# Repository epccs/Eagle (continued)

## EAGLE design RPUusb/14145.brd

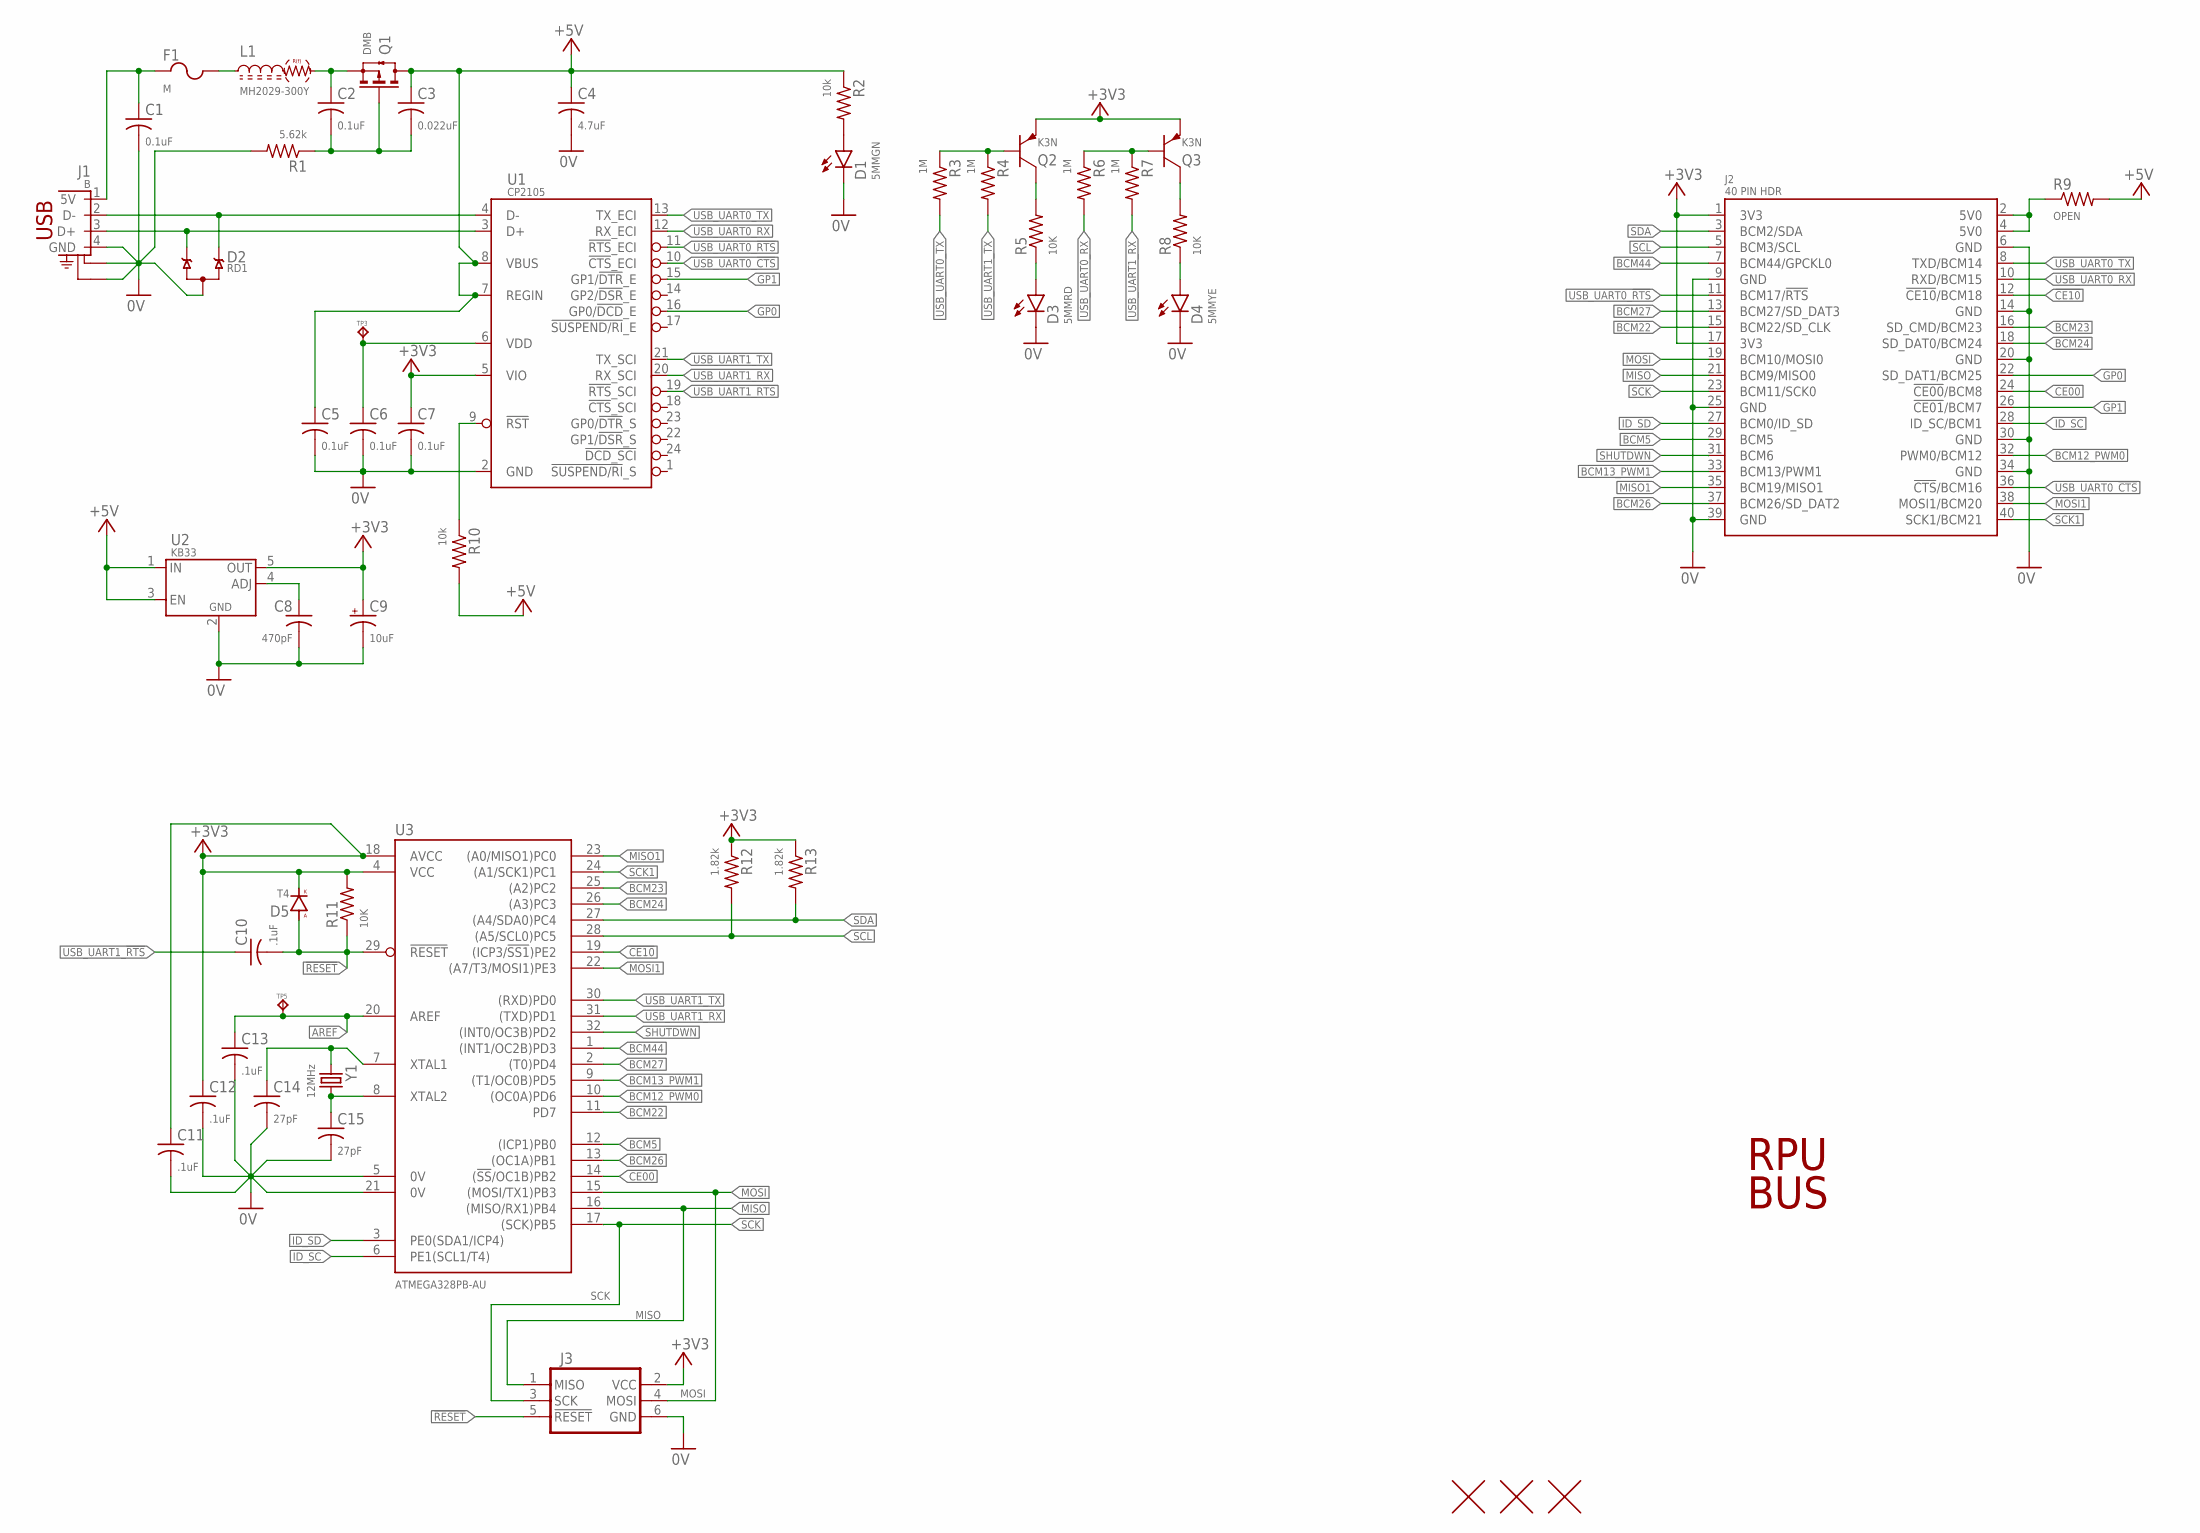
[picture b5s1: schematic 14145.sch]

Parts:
C1, C2, C5, C6, C7: 0.1uF; C0603(1608)
C3: 0.022uF; C0603(1608)
C4: 4.7uF; C1206(3216)
C8: 470pF; C0603(1608)
C9: 10uF; 3216
C10, C11, C12, C13: .1uF; C0603(1608)
C14, C15: 27pF; C0603(1608)
D1: 5MMGN; LED5MM
D2: RD1; SOT23
D3: 5MMRD; LED5MM
D4: 5MMYE; LED5MM
D5: T4; SOD123
F1: M; C1210(3225)
J1: B; USB-B-PTH
J2: 40 PIN HDR; RASPI_ZERO_H40PIN
J3: ISP-SPIPTH; ISP
L1: MH2029-300Y; C0805(2012)
Q1: DMB; SOT23
Q2, Q3: K3N; SOT23
R1: 5.62k; C0805(2012)
R2, R10: 10k; C0805(2012)
R3, R4, R6, R7: 1M; C0805(2012)
R5, R8, R11: 10K; C0805(2012)
R9: OPEN; C0805(2012)
R12, R13: 1.82k; C0805(2012)
TP3, TP5: TPPAD1-08; P1-08
U1: CP2105; QFN24
U2: KB33; SOT23-5,SOT25
U3: ATMEGA328PB-AU; TQFP32-08
U$2, U$3, U$4: FIDUCIAL1.27; FIDUCIAL-1.27
Y1: 12MHz; CSM-3X

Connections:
0V: C1.2, C4.2, C5.2, C6.2, C7.2, C8.2, C9.-, C11.2, C12.2, C13.2, C14.2, C15.2, D1.K, D2.3 (A), D3.K, D4.K, J1.4 (GND), J1.S1 (CHASSIS1), J1.S2 (CHASSIS2), J2.6 (GND), J2.9 (GND), J2.14 (GND), J2.20 (GND), J2.25 (GND), J2.30 (GND), J2.34 (GND), J2.39 (GND), J3.6 (GND), R1.2, U1.2 (GND), U2.2 (GND), U3.5 (0V), U3.21 (0V)
5V0@2: J2.2 (5V0), J2.4 (5V0), R9.1
!CE00!: J2.24 (!CE00!/BCM8), U3.14 ((!SS!/OC1B)PB2)
!CE10!: J2.12 (!CE10!/BCM18), U3.19 ((ICP3/!SS1!)PE2)
!RESET: C10.2, D5.A, J3.5 (!RESET), R11.1, U3.29 (!RESET)
+3V3: C7.1, C9.+, C11.1, C12.1, D5.C (K), J2.1 (3V3), J2.17 (3V3), J3.2 (VCC), Q2.E, Q3.E, R11.2, R12.1, R13.1, U1.5 (VIO), U2.5 (OUT), U3.4 (VCC), U3.18 (AVCC)
+5V: C3.1, C4.1, C5.1, Q1.3(D) (D), R2.1, R9.2, R10.2, U1.7 (REGIN), U1.8 (VBUS), U2.1 (IN), U2.3 (EN)
AREF: C13.1, TP5.TP, U3.20 (AREF)
BCM5: J2.29 (BCM5), U3.12 ((ICP1)PB0)
BCM12_PWM0: J2.32 (PWM0/BCM12), U3.10 ((OC0A)PD6)
BCM13_PWM1: J2.33 (BCM13/PWM1), U3.9 ((T1/OC0B)PD5)
BCM22: J2.15 (BCM22/SD_CLK), U3.11 (PD7)
BCM23: J2.16 (SD_CMD/BCM23), U3.25 ((A2)PC2)
BCM24: J2.18 (SD_DAT0/BCM24), U3.26 ((A3)PC3)
BCM26: J2.37 (BCM26/SD_DAT2), U3.13 ((OC1A)PB1)
BCM27: J2.13 (BCM27/SD_DAT3), U3.2 ((T0)PD4)
BCM44: J2.7 (BCM44/GPCKL0), U3.1 ((INT1/OC2B)PD3)
D+: D2.1 (C1), J1.3 (D+), U1.3 (D+)
D-: D2.2 (C2), J1.2 (D-), U1.4 (D-)
FTDI3V3: C6.1, TP3.TP, U1.6 (VDD)
GP0: J2.22 (SD_DAT1/BCM25), U1.16 (GP0/!DCD!_E)
GP1: J2.26 (!CE01!/BCM7), U1.15 (GP1/!DTR!_E)
ID_SC: J2.28 (ID_SC/BCM1), U3.6 (PE1(SCL1/T4))
ID_SD: J2.27 (BCM0/ID_SD), U3.3 (PE0(SDA1/ICP4))
MISO: J2.21 (BCM9/MISO0), J3.1 (MISO), U3.16 ((MISO/RX1)PB4)
MISO1: J2.35 (BCM19/MISO1), U3.23 ((A0/MISO1)PC0)
MOSI: J2.19 (BCM10/MOSI0), J3.4 (MOSI), U3.15 ((MOSI/TX1)PB3)
MOSI1: J2.38 (MOSI1/BCM20), U3.22 ((A7/T3/MOSI1)PE3)
unnamed: D1.A, R2.2
unnamed: D4.A, R8.1
unnamed: Q3.C, R8.2
unnamed: C1.1, F1.1, J1.1 (5V)
unnamed: F1.2, L1.1
unnamed: D3.A, R5.1
unnamed: R10.1, U1.9 (!RST!)
unnamed: Q2.C, R5.2
unnamed: Q2.B, R3.1, R4.1
unnamed: Q3.B, R6.1, R7.1
unnamed: C8.1, U2.4 (ADJ)
unnamed: C2.1, L1.2, Q1.2(S) (S)
unnamed: C2.2, C3.2, Q1.1(G) (G), R1.1
SCK: J2.23 (BCM11/SCK0), J3.3 (SCK), U3.17 ((SCK)PB5)
SCK1: J2.40 (SCK1/BCM21), U3.24 ((A1/SCK1)PC1)
SCL: J2.5 (BCM3/SCL), R12.2, U3.28 ((A5/SCL0)PC5)
SDA: J2.3 (BCM2/SDA), R13.2, U3.27 ((A4/SDA0)PC4)
SHUTDWN: J2.31 (BCM6), U3.32 ((INT0/OC3B)PD2)
USB_UART0_!CTS: J2.36 (!CTS!/BCM16), U1.10 (!CTS!_ECI)
USB_UART0_!RTS: J2.11 (BCM17/!RTS!), U1.11 (!RTS!_ECI)
USB_UART0_RX: J2.10 (RXD/BCM15), R6.2, U1.12 (RX_ECI)
USB_UART0_TX: J2.8 (TXD/BCM14), R3.2, U1.13 (TX_ECI)
USB_UART1_!RTS: C10.1, U1.19 (!RTS!_SCI)
USB_UART1_RX: R7.2, U1.20 (RX_SCI), U3.31 ((TXD)PD1)
USB_UART1_TX: R4.2, U1.21 (TX_SCI), U3.30 ((RXD)PD0)
XTAL1: C14.1, U3.7 (XTAL1), Y1.1
XTAL2: C15.1, U3.8 (XTAL2), Y1.2

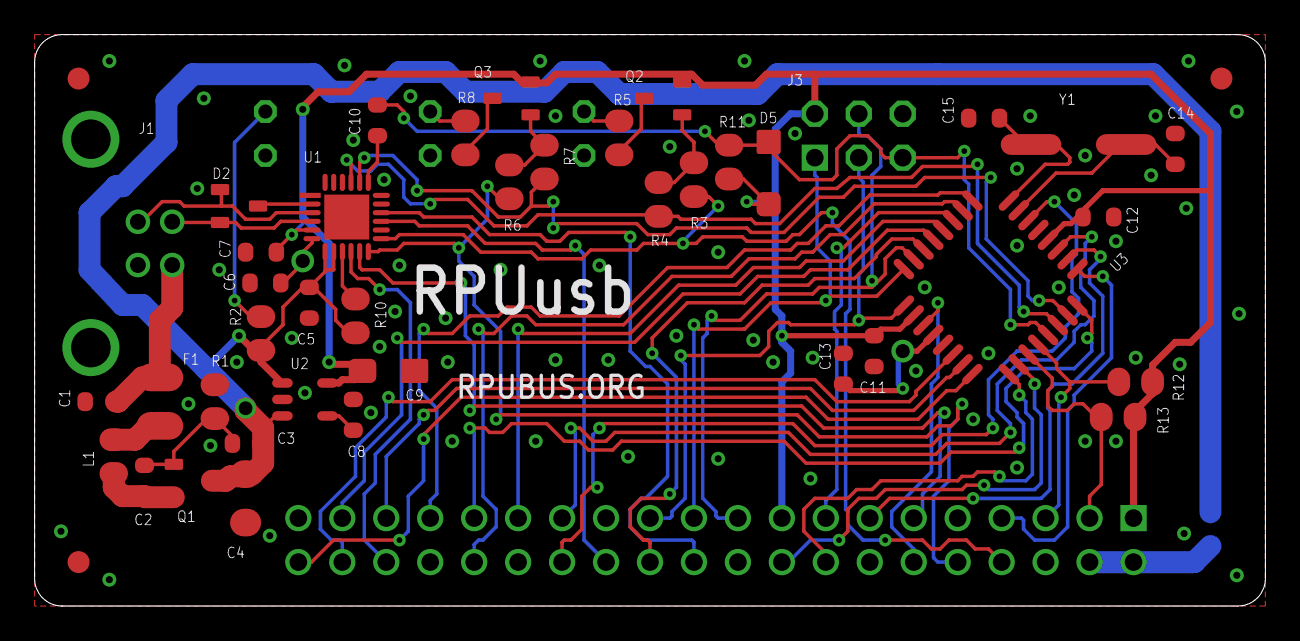
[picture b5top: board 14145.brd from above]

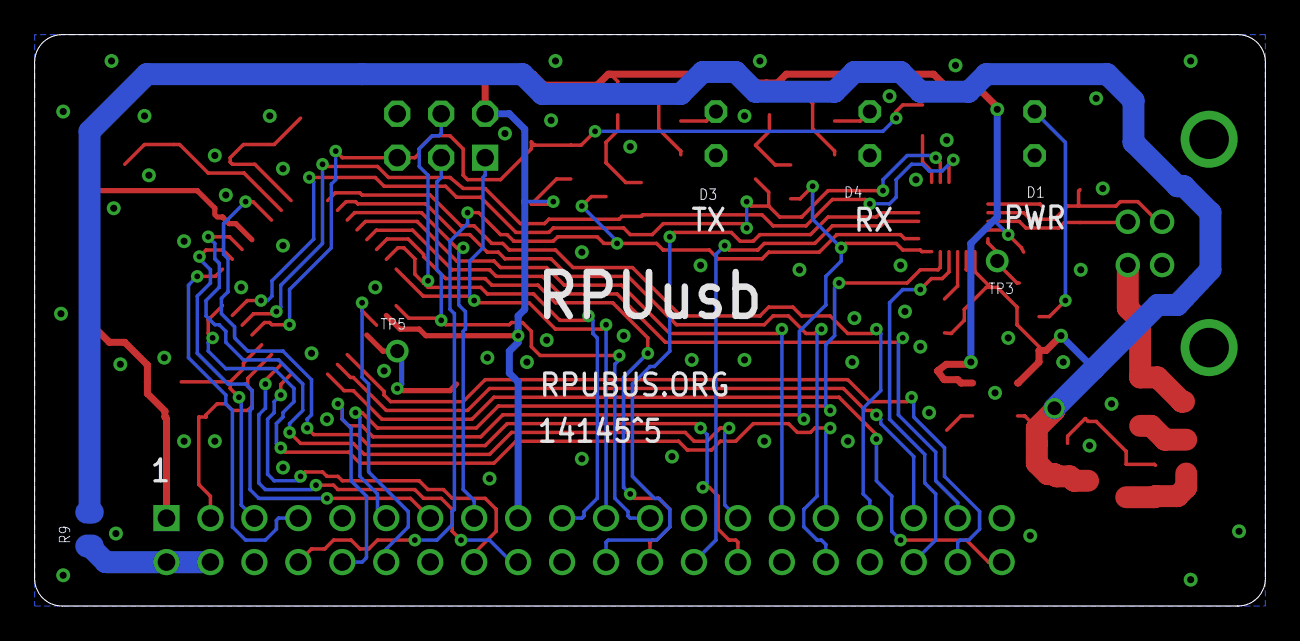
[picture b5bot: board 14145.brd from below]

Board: 2 copper layers, 71.1 x 33.0 mm, 50 parts (6 on the bottom side), 55 nets.

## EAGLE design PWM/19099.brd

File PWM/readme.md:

PWM

Sixteen 22mA current sources controled with PCA9685 over I2C

TBD https://oshpark.com/shared_projects/???

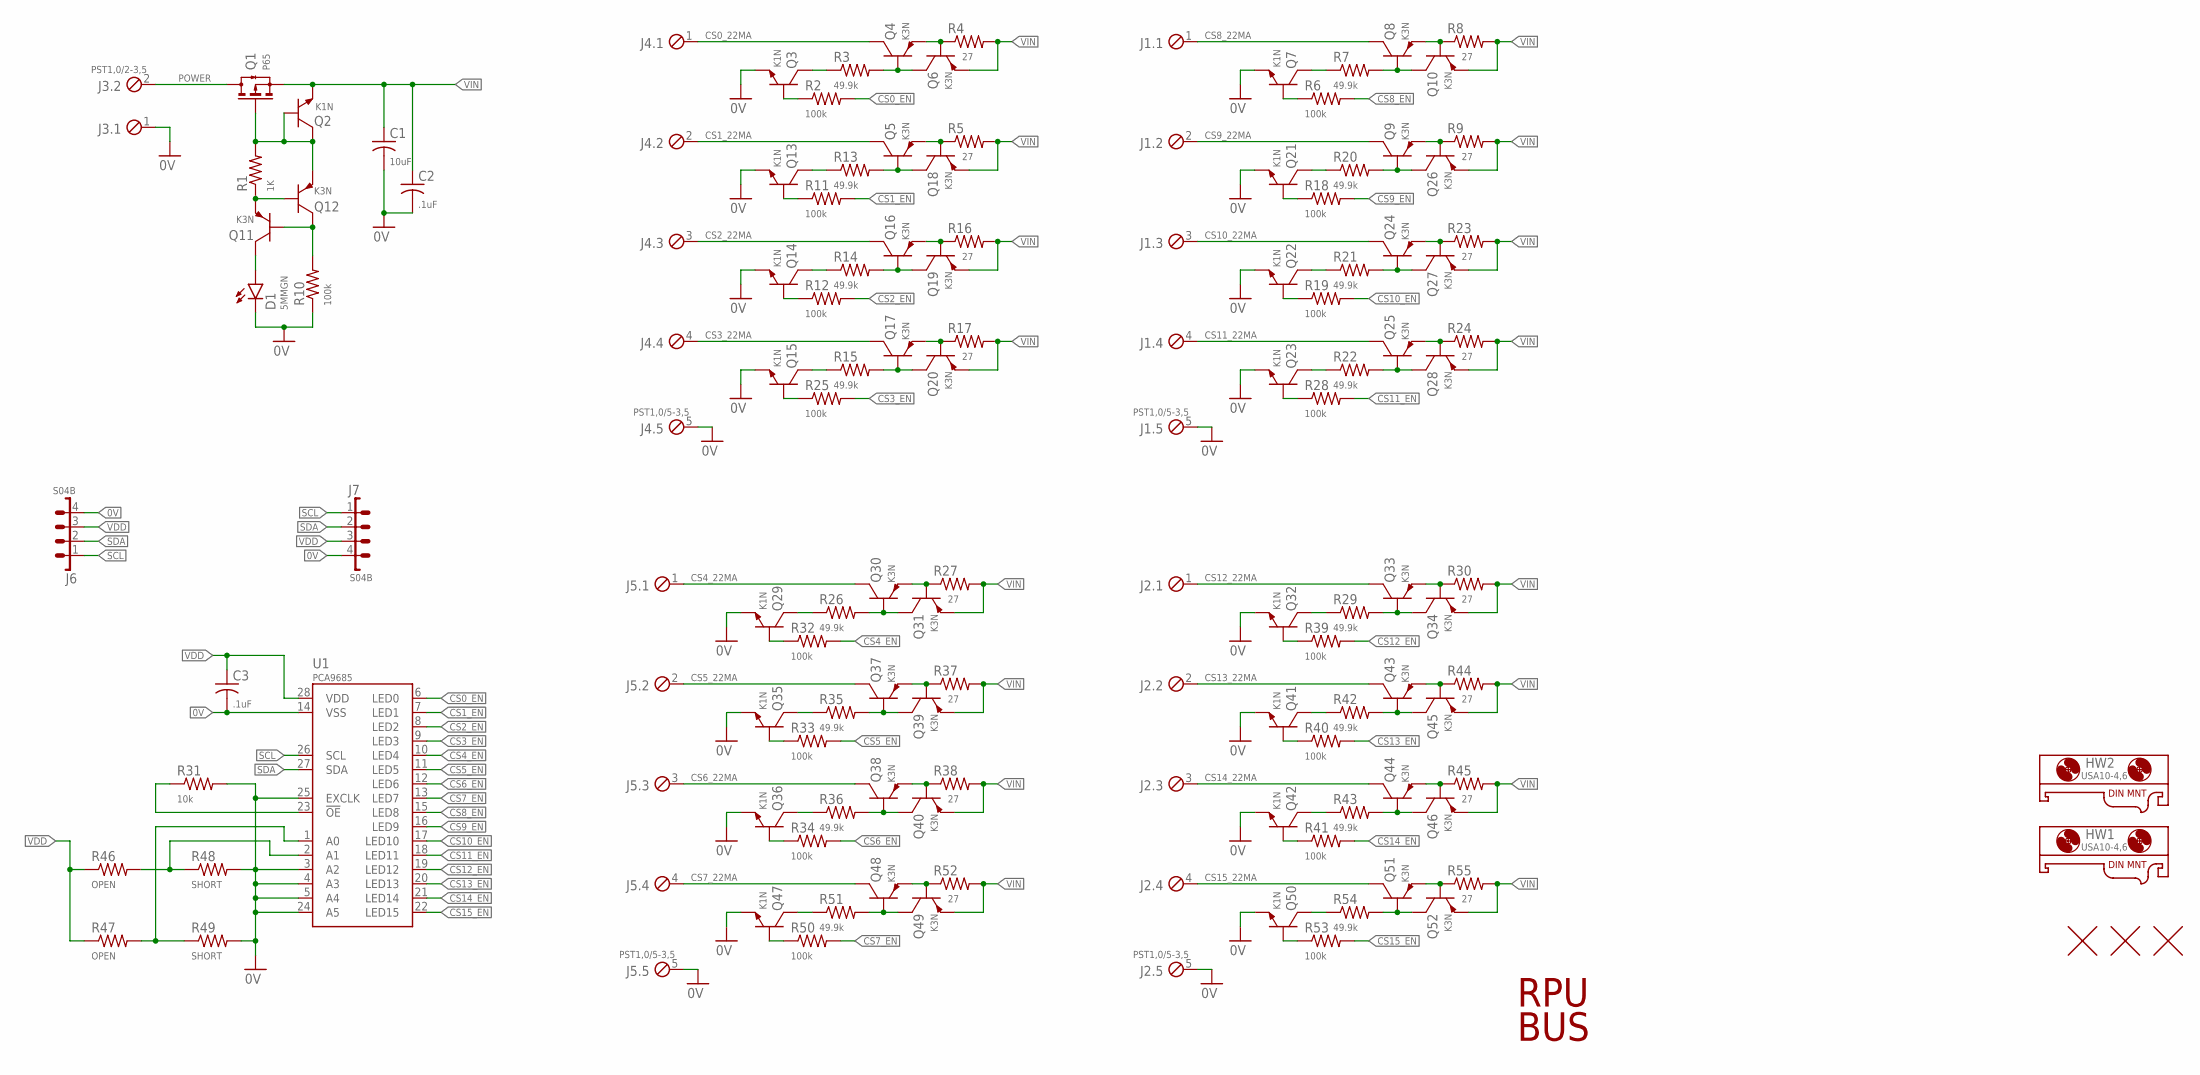
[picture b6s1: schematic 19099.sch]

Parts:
C1: 10uF; C1206(3216)
C2: .1uF; C0805(2012)
C3: .1uF; C0603(1608)
D1: 5MMGN; LED5MM
HW1, HW2: USA10-4,6; USA10
J1, J2, J4, J5: PST1,0/5-3,5; MCV5
J3: PST1,0/2-3,5; MCV2
J6, J7: S04B; B04B
Q1: P65; SOT23
Q2, Q3, Q7, Q13, Q14, Q15, Q21, Q22, Q23, Q29, Q32, Q35, Q36, Q41, Q42, Q47, Q50: K1N; SOT23
Q4, Q5, Q6, Q8, Q9, Q10, Q11, Q12, Q16, Q17, Q18, Q19, Q20, Q24, Q25, Q26, Q27, Q28, Q30, Q31, Q33, Q34, Q37, Q38, Q39, Q40, Q43, Q44, Q45, Q46, Q48, Q49, Q51, Q52: K3N; SOT23
R1: 1K; C0805(2012)
R2, R6, R10, R11, R12, R18, R19, R25, R28, R32, R33, R34, R39, R40, R41, R50, R53: 100k; C0805(2012)
R3, R7, R13, R14, R15, R20, R21, R22, R26, R29, R35, R36, R42, R43, R51, R54: 49.9k; C0805(2012)
R4, R5, R8, R9, R16, R17, R23, R24, R27, R30, R37, R38, R44, R45, R52, R55: 27; C0805(2012)
R31: 10k; C0805(2012)
R46, R47: OPEN; C0805(2012)
R48, R49: SHORT; C0805(2012)
U1: PCA9685; 28TSSOP
U$2, U$3, U$4: FIDUCIAL1.27; FIDUCIAL-1.27

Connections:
0V: C1.2, C2.2, C3.2, D1.K, J1.5, J2.5, J3.1, J4.5, J5.5, J6.4, J7.4, Q3.E, Q7.E, Q13.E, Q14.E, Q15.E, Q21.E, Q22.E, Q23.E, Q29.E, Q32.E, Q35.E, Q36.E, Q41.E, Q42.E, Q47.E, Q50.E, R10.1, R31.2, R48.2, R49.2, U1.3 (A2), U1.4 (A3), U1.5 (A4), U1.14 (VSS), U1.24 (A5), U1.25 (EXCLK)
A0: R47.2, R49.1, U1.1 (A0)
A1: R46.2, R48.1, U1.2 (A1)
CS0_22MA: J4.1, Q4.C
CS0_EN: R2.2, U1.6 (LED0)
CS1_22MA: J4.2, Q5.C
CS1_EN: R11.2, U1.7 (LED1)
CS2_22MA: J4.3, Q16.C
CS2_EN: R12.2, U1.8 (LED2)
CS3_22MA: J4.4, Q17.C
CS3_EN: R25.2, U1.9 (LED3)
CS4_22MA: J5.1, Q30.C
CS4_EN: R32.2, U1.10 (LED4)
CS5_22MA: J5.2, Q37.C
CS5_EN: R33.2, U1.11 (LED5)
CS6_22MA: J5.3, Q38.C
CS6_EN: R34.2, U1.12 (LED6)
CS7_22MA: J5.4, Q48.C
CS7_EN: R50.2, U1.13 (LED7)
CS8_22MA: J1.1, Q8.C
CS8_EN: R6.2, U1.15 (LED8)
CS9_22MA: J1.2, Q9.C
CS9_EN: R18.2, U1.16 (LED9)
CS10_22MA: J1.3, Q24.C
CS10_EN: R19.2, U1.17 (LED10)
CS11_22MA: J1.4, Q25.C
CS11_EN: R28.2, U1.18 (LED11)
CS12_22MA: J2.1, Q33.C
CS12_EN: R39.2, U1.19 (LED12)
CS13_22MA: J2.2, Q43.C
CS13_EN: R40.2, U1.20 (LED13)
CS14_22MA: J2.3, Q44.C
CS14_EN: R41.2, U1.21 (LED14)
CS15_22MA: J2.4, Q51.C
CS15_EN: R53.2, U1.22 (LED15)
unnamed: Q4.E, Q6.B, R4.1
unnamed: Q3.B, R2.1
unnamed: Q5.E, Q18.B, R5.1
unnamed: Q5.B, Q18.C, R13.2
unnamed: Q11.B, Q12.C, R10.2
unnamed: Q1.1(G) (G), Q2.B, Q2.C, Q12.E, R1.2
unnamed: D1.A, Q11.C
unnamed: Q13.C, R13.1
unnamed: Q4.B, Q6.C, R3.2
unnamed: Q11.E, Q12.B, R1.1
unnamed: Q13.B, R11.1
unnamed: Q16.E, Q19.B, R16.1
unnamed: Q16.B, Q19.C, R14.2
unnamed: Q14.C, R14.1
unnamed: Q14.B, R12.1
unnamed: Q17.E, Q20.B, R17.1
unnamed: Q17.B, Q20.C, R15.2
unnamed: Q15.C, R15.1
unnamed: Q15.B, R25.1
unnamed: R31.1, U1.23 (!OE)
unnamed: Q30.E, Q31.B, R27.1
unnamed: Q30.B, Q31.C, R26.2
unnamed: Q29.C, R26.1
unnamed: Q29.B, R32.1
unnamed: Q37.E, Q39.B, R37.1
unnamed: Q37.B, Q39.C, R35.2
unnamed: Q35.C, R35.1
unnamed: Q35.B, R33.1
unnamed: Q38.E, Q40.B, R38.1
unnamed: Q38.B, Q40.C, R36.2
unnamed: Q36.C, R36.1
unnamed: Q36.B, R34.1
unnamed: Q48.E, Q49.B, R52.1
unnamed: Q48.B, Q49.C, R51.2
unnamed: Q47.C, R51.1
unnamed: Q47.B, R50.1
unnamed: Q8.E, Q10.B, R8.1
unnamed: Q8.B, Q10.C, R7.2
unnamed: Q7.C, R7.1
unnamed: Q7.B, R6.1
unnamed: Q9.E, Q26.B, R9.1
unnamed: Q9.B, Q26.C, R20.2
unnamed: Q21.C, R20.1
unnamed: Q21.B, R18.1
unnamed: Q24.E, Q27.B, R23.1
unnamed: Q24.B, Q27.C, R21.2
unnamed: Q22.C, R21.1
unnamed: Q22.B, R19.1
unnamed: Q25.E, Q28.B, R24.1
unnamed: Q25.B, Q28.C, R22.2
unnamed: Q23.C, R22.1
unnamed: Q23.B, R28.1
unnamed: Q33.E, Q34.B, R30.1
unnamed: Q33.B, Q34.C, R29.2
unnamed: Q32.C, R29.1
unnamed: Q32.B, R39.1
unnamed: Q43.E, Q45.B, R44.1
unnamed: Q3.C, R3.1
unnamed: Q43.B, Q45.C, R42.2
unnamed: Q41.C, R42.1
unnamed: Q41.B, R40.1
unnamed: Q44.E, Q46.B, R45.1
unnamed: Q44.B, Q46.C, R43.2
unnamed: Q42.C, R43.1
unnamed: Q42.B, R41.1
unnamed: Q51.E, Q52.B, R55.1
unnamed: Q51.B, Q52.C, R54.2
unnamed: Q50.C, R54.1
unnamed: Q50.B, R53.1
POWER: J3.2, Q1.3(D) (D)
SCL: J6.1, J7.1, U1.26 (SCL)
SDA: J6.2, J7.2, U1.27 (SDA)
VDD: C3.1, J6.3, J7.3, R46.1, R47.1, U1.28 (VDD)
VIN: C1.1, C2.1, Q1.2(S) (S), Q2.E, Q6.E, Q10.E, Q18.E, Q19.E, Q20.E, Q26.E, Q27.E, Q28.E, Q31.E, Q34.E, Q39.E, Q40.E, Q45.E, Q46.E, Q49.E, Q52.E, R4.2, R5.2, R8.2, R9.2, R16.2, R17.2, R23.2, R24.2, R27.2, R30.2, R37.2, R38.2, R44.2, R45.2, R52.2, R55.2

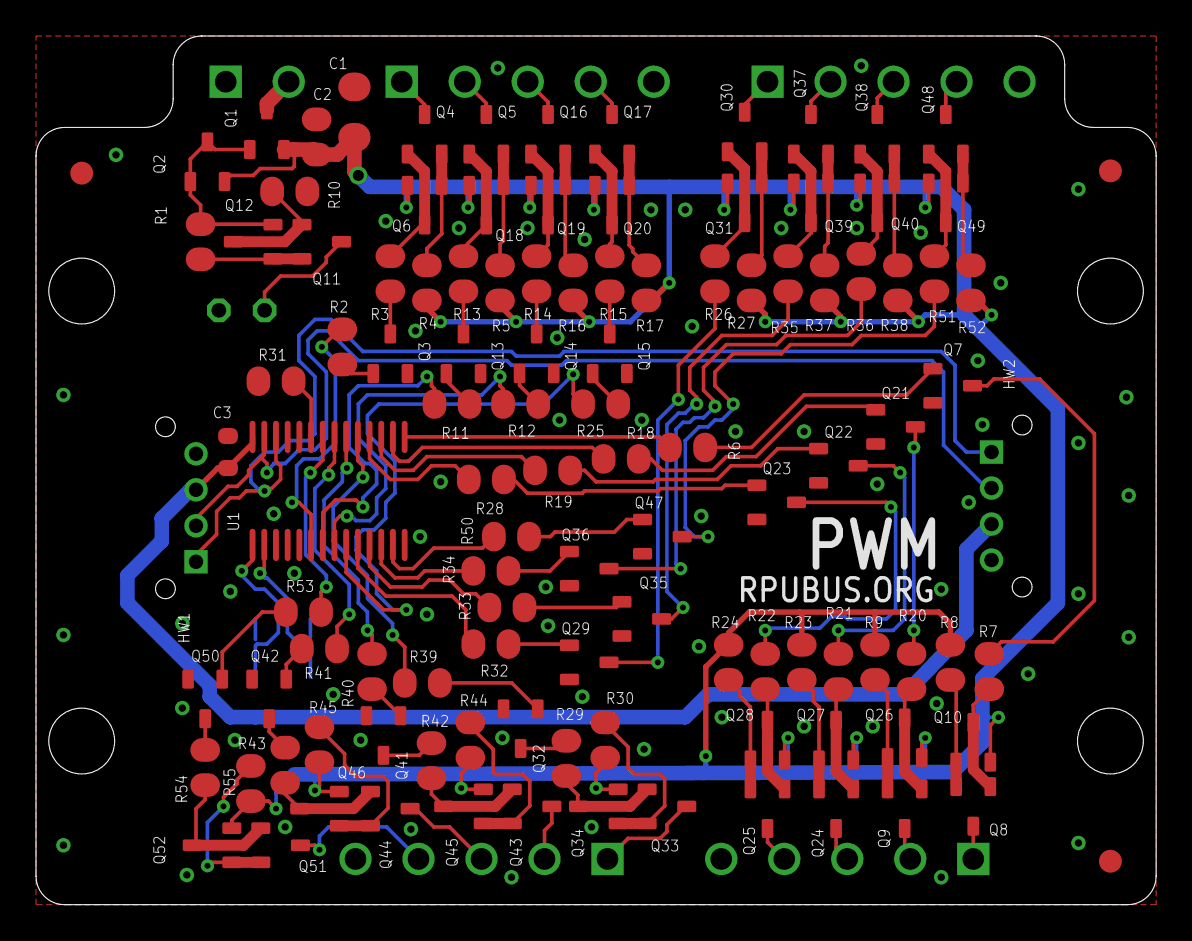
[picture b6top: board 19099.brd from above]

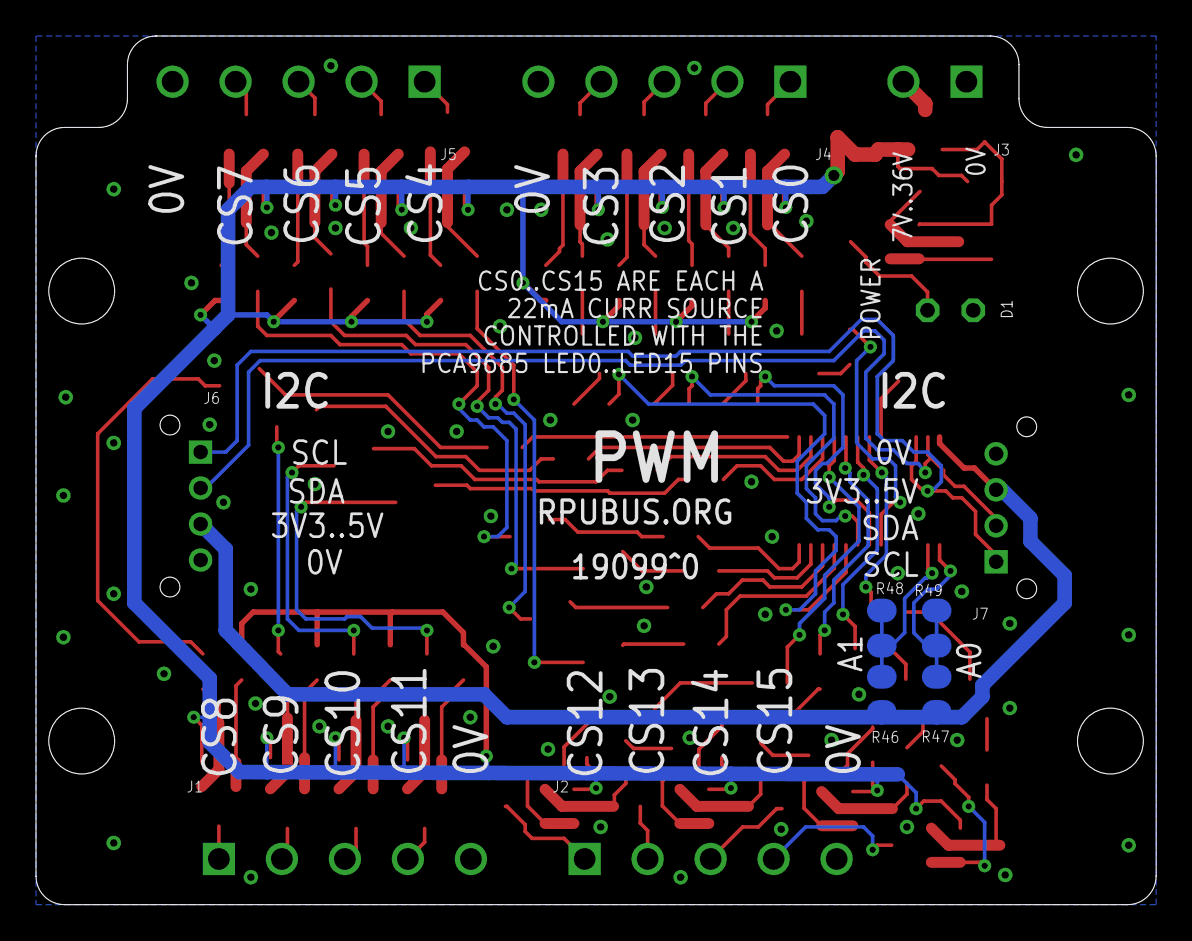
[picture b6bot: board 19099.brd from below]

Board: 2 copper layers, 62.2 x 48.3 mm, 124 parts (12 on the bottom side), 109 nets.

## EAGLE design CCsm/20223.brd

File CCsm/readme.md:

CCsm

Small constant current source for LED and other uses. Negative temperature coefficient (NTC) reduces current (thermal fold-back) with increasing temperature (about 0.2 %/K)

https://oshpark.com/shared_projects/9gUEmC1T

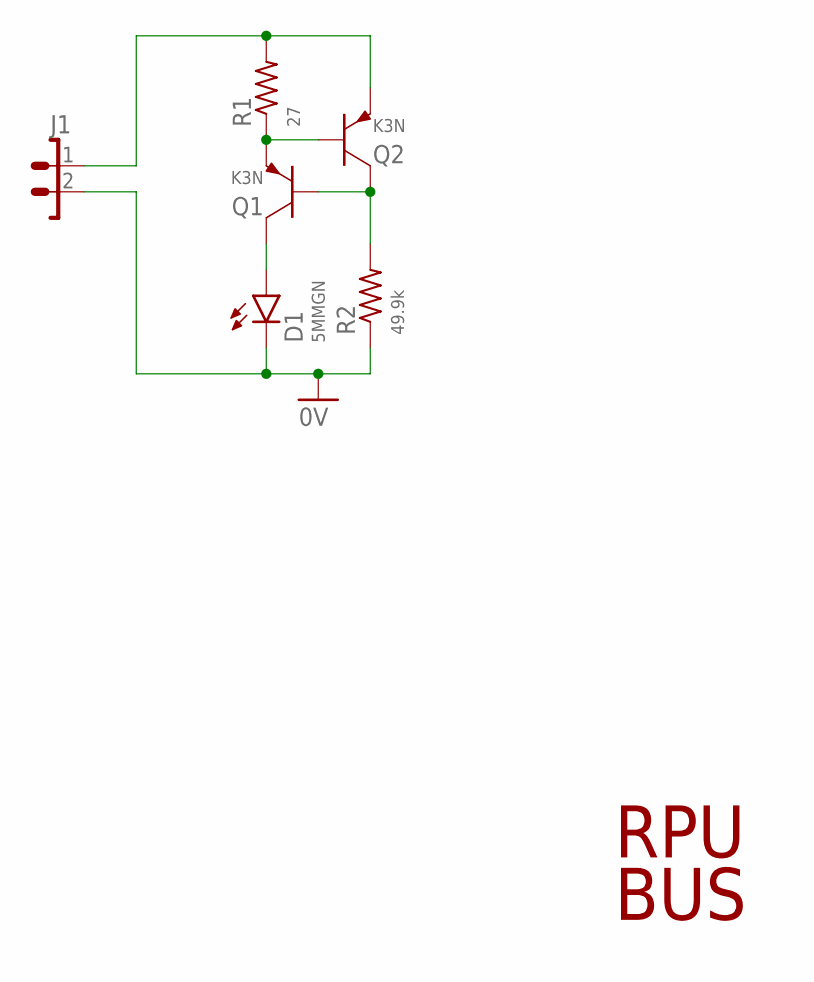
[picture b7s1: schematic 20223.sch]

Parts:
D1: 5MMGN; LED5MM
J1: 1X2
Q1, Q2: K3N; SOT23
R1: 27; C0805(2012)
R2: 49.9k; C0805(2012)

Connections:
0V: D1.K, J1.2, R2.1
unnamed: Q1.B, Q2.C, R2.2
unnamed: J1.1, Q2.E, R1.2
unnamed: D1.A, Q1.C
unnamed: Q1.E, Q2.B, R1.1

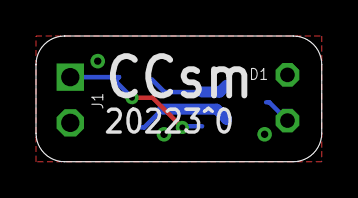
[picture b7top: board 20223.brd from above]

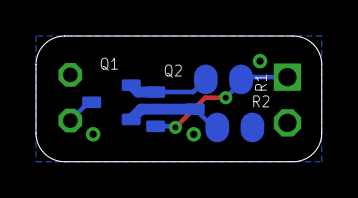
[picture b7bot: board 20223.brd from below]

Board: 2 copper layers, 15.9 x 7.0 mm, 6 parts (4 on the bottom side), 5 nets.

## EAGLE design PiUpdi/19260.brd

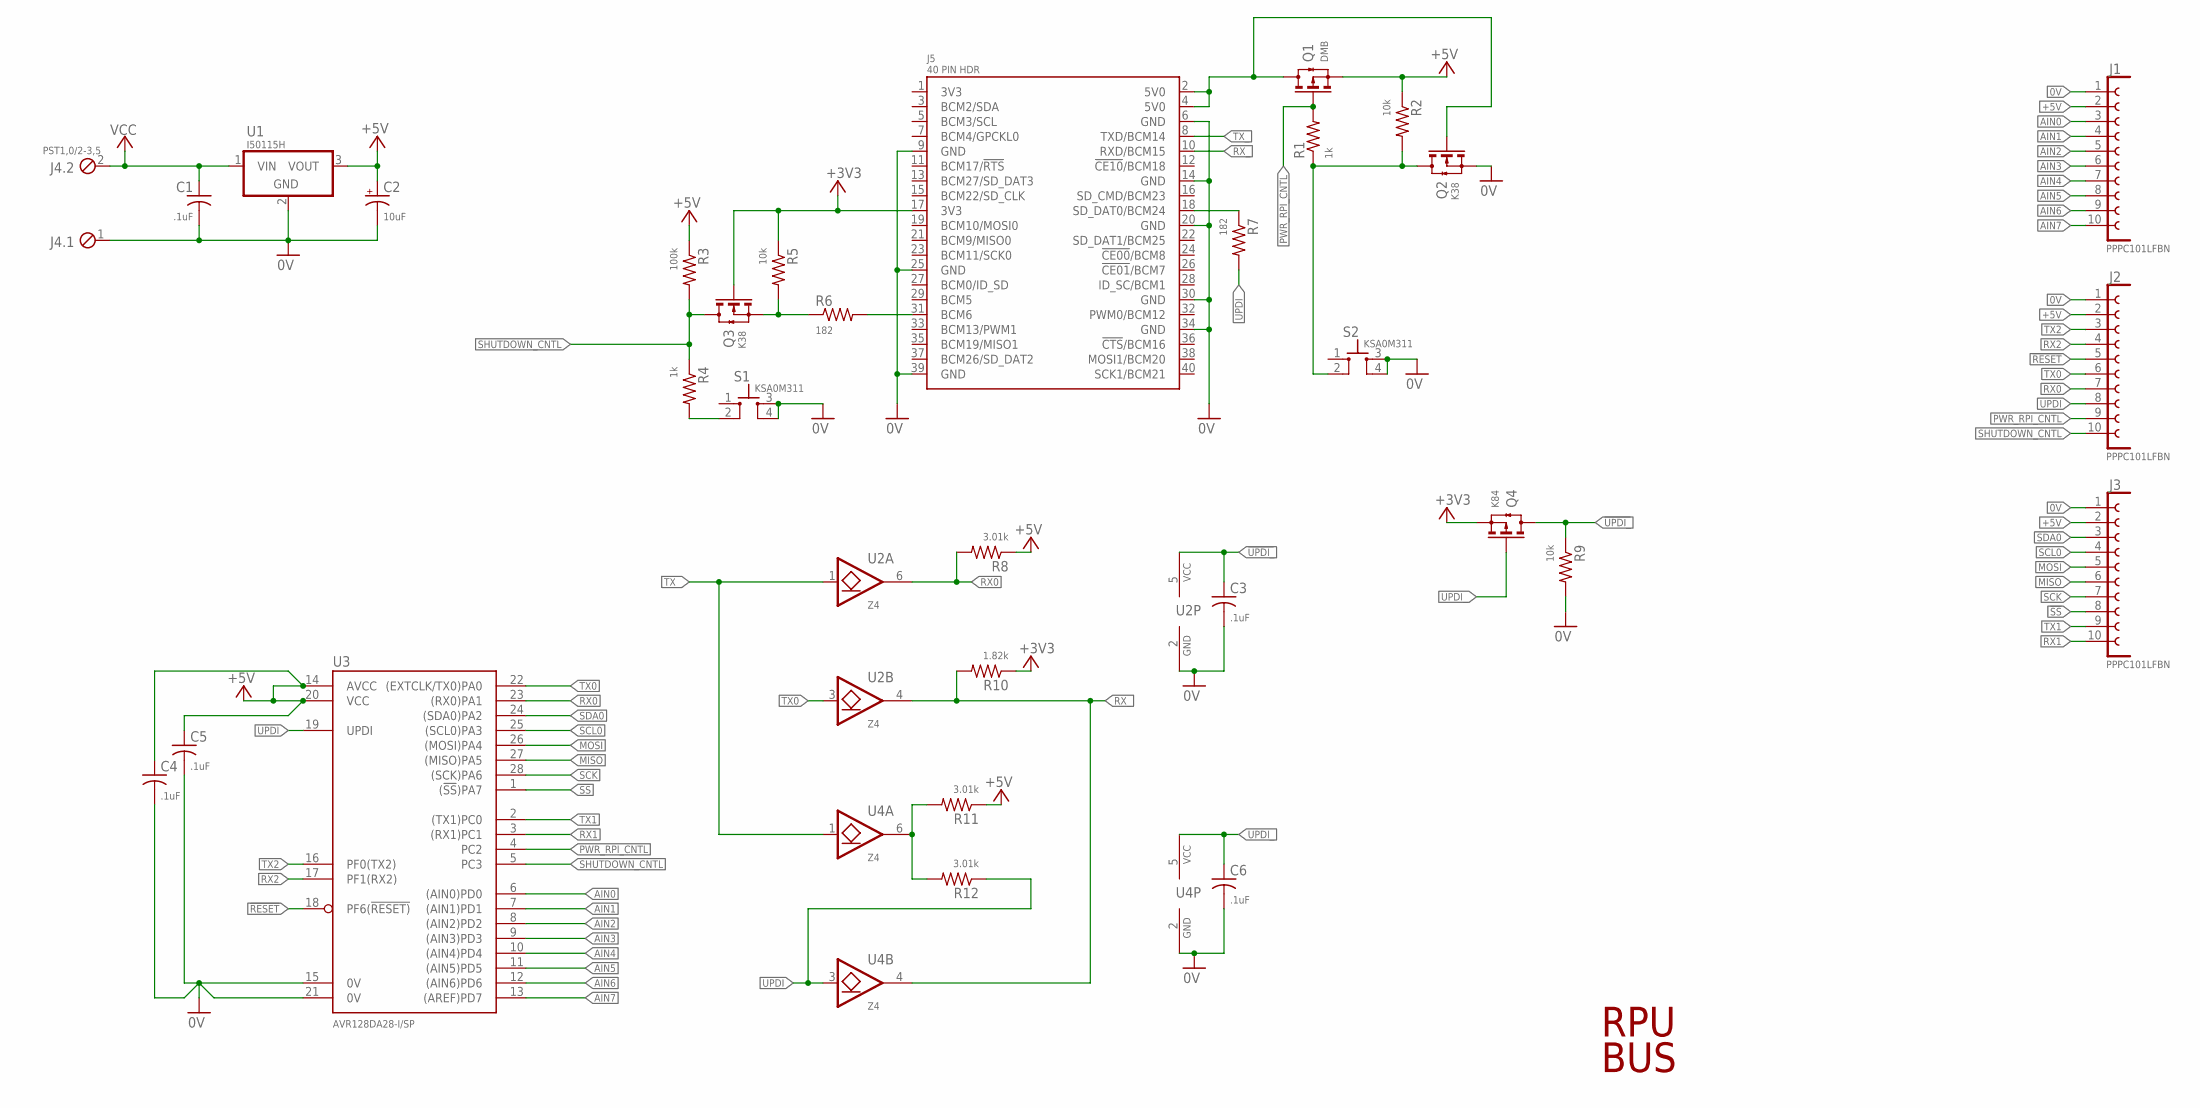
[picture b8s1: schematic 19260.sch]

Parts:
C1, C3, C4, C5, C6: .1uF; C0603(1608)
C2: 10uF; 3216
J1, J2, J3: PPPC101LFBN; F1X10
J4: PST1,0/2-3,5; MCV2
J5: 40 PIN HDR; RASPI_ZERO_H40PIN
Q1: DMB; SOT23
Q2, Q3: K38; SOT23
Q4: K84; SOT23
R1, R4: 1k; C0805(2012)
R2, R5, R9: 10k; C0805(2012)
R3: 100k; C0805(2012)
R6, R7: 182; C0805(2012)
R8, R11, R12: 3.01k; C0805(2012)
R10: 1.82k; C0805(2012)
S1, S2: KSA0M311; 0M311
U1: I50115H; OKI-78SR-H
U2, U4: Z4; SOT23-6,SOT26
U3: AVR128DA28-I/SP; DIL28-3

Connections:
0V: C1.2, C2.-, C3.2, C4.2, C5.2, C6.2, J1.1, J2.1, J3.1, J4.1, J5.6 (GND), J5.9 (GND), J5.14 (GND), J5.20 (GND), J5.25 (GND), J5.30 (GND), J5.34 (GND), J5.39 (GND), Q2.2(S) (S), R9.2, S1.3, S1.4, S2.3, S2.4, U1.2 (GND), U2.2 (GND), U3.15 (0V), U3.21 (0V), U4.2 (GND)
5V0@2: J5.2 (5V0), J5.4 (5V0), Q1.3(D) (D), Q2.1(G) (G)
!RESET: J2.5, U3.18 (PF6(!RESET))
!SS: J3.8, U3.1 ((!SS!)PA7)
!UPDI_: C3.1, Q4.3(D) (D), R9.1, U2.5 (VCC)
+3V3: J5.17 (3V3), Q3.1(G) (G), Q4.2(S) (S), R5.1, R10.1
+5V: C2.+, C4.1, C5.1, J1.2, J2.2, J3.2, Q1.2(S) (S), R2.1, R3.1, R8.1, R11.1, U1.3 (VOUT), U3.14 (AVCC), U3.20 (VCC)
AIN0: J1.3, U3.6 ((AIN0)PD0)
AIN1: J1.4, U3.7 ((AIN1)PD1)
AIN2: J1.5, U3.8 ((AIN2)PD2)
AIN3: J1.6, U3.9 ((AIN3)PD3)
AIN4: J1.7, U3.10 ((AIN4)PD4)
AIN5: J1.8, U3.11 ((AIN5)PD5)
AIN6: J1.9, U3.12 ((AIN6)PD6)
AIN7: J1.10, U3.13 ((AREF)PD7)
MISO: J3.6, U3.27 ((MISO)PA5)
MOSI: J3.5, U3.26 ((MOSI)PA4)
unnamed: R4.2, S1.2
unnamed: J5.18 (SD_DAT0/BCM24), R7.1
unnamed: J5.31 (BCM6), R6.2
unnamed: R11.2, R12.2, U4.6 (O)
unnamed: Q2.3(D) (D), R1.1, R2.2, S2.2
PWR_RPI_CNTL: J2.9, Q1.1(G) (G), R1.2, U3.4 (PC2)
RX0: J2.7, R8.2, U2.6 (O), U3.23 ((RX0)PA1)
RX1: J3.10, U3.3 ((RX1)PC1)
RX2: J2.4, U3.17 (PF1(RX2))
RX_: J5.10 (RXD/BCM15), R10.2, U2.4 (O), U4.4 (O)
SCK: J3.7, U3.28 ((SCK)PA6)
SCL0: J3.4, U3.25 ((SCL0)PA3)
SDA0: J3.3, U3.24 ((SDA0)PA2)
SHUTDOWN: Q3.2(S) (S), R5.2, R6.1
SHUTDOWN_CNTL: J2.10, Q3.3(D) (D), R3.2, R4.1, U3.5 (PC3)
TX0: J2.6, U2.3 (I), U3.22 ((EXTCLK/TX0)PA0)
TX1: J3.9, U3.2 ((TX1)PC0)
TX2: J2.3, U3.16 (PF0(TX2))
TX_: J5.8 (TXD/BCM14), U2.1 (I), U4.1 (I)
UPDI: J2.8, R12.1, U3.19 (UPDI), U4.3 (I)
UPDI_: C6.1, Q4.1(G) (G), R7.2, U4.5 (VCC)
VCC: C1.1, J4.2, U1.1 (VIN)

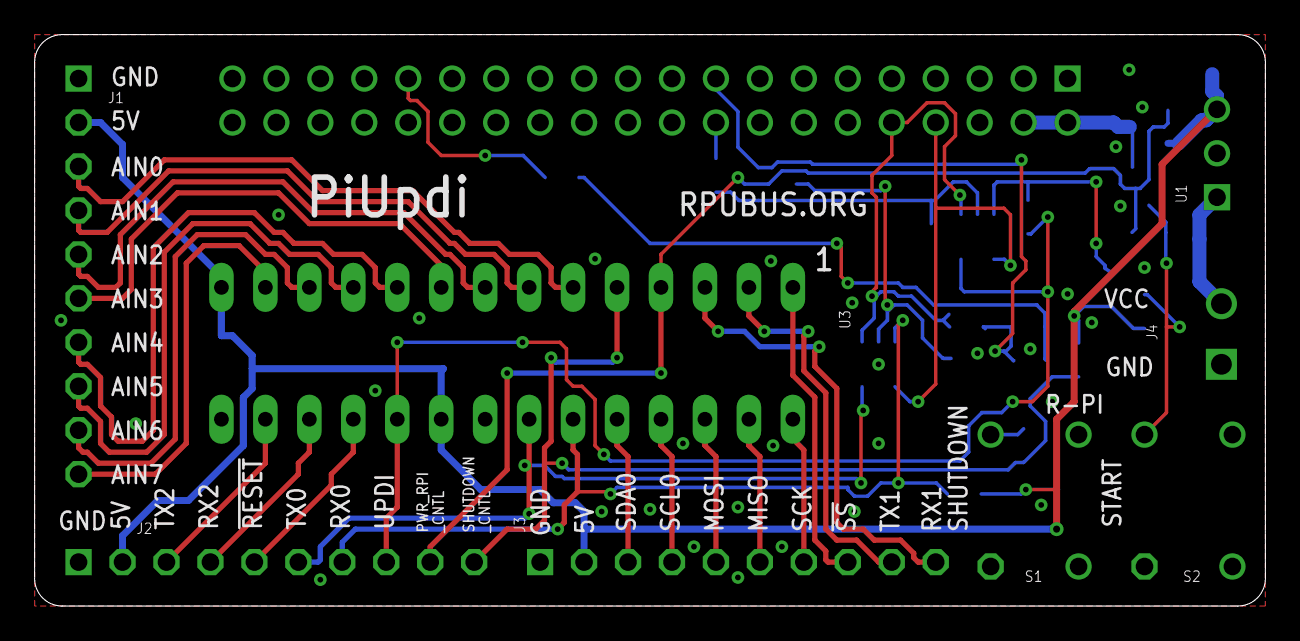
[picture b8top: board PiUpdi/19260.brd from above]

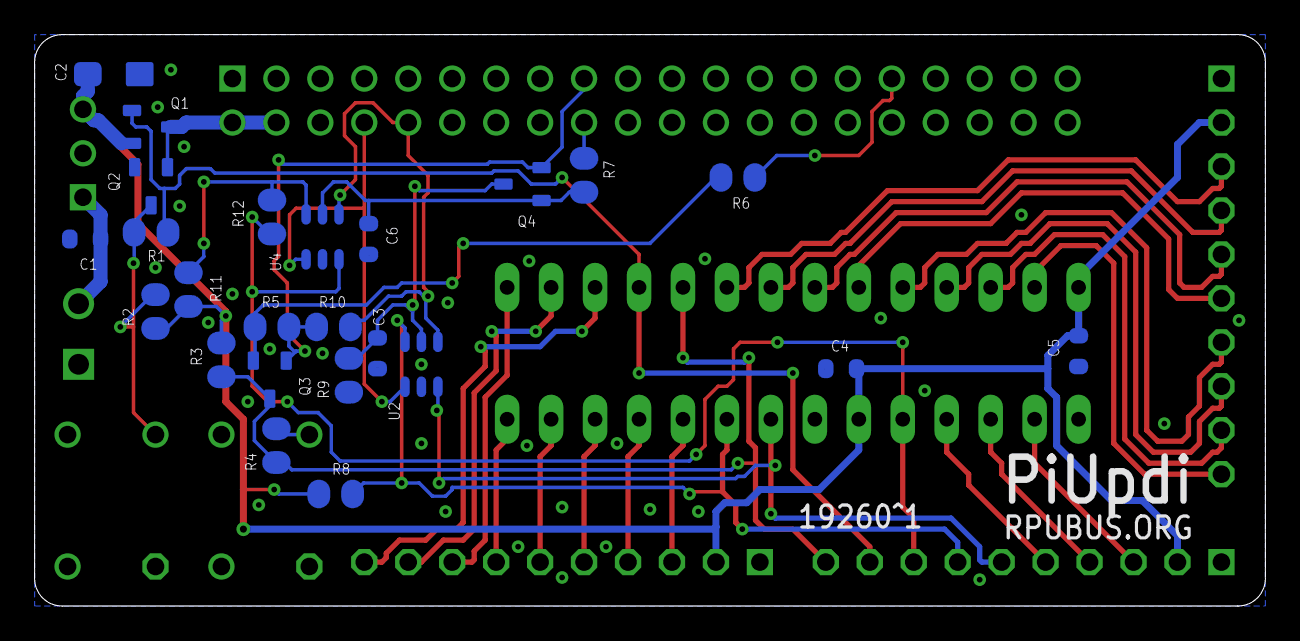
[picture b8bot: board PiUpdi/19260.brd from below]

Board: 2 copper layers, 71.1 x 33.0 mm, 33 parts (24 on the bottom side), 39 nets.

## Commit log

2017-11-12 :circus_tent: Added .gitattributes
2017-11-13 RPUno: add some of past versions
2017-11-15 RPUadpt: some past versions
2017-12-19 add RPUftdi, RPUpi and new RPUno
2017-12-19 notes
2018-01-17 RPUlux^0 as built and now in testing
2018-01-27 Irrigate7: ^4 was never made or tested
    the solar charge control is going to be removed and that will cause a
    lot of other changes.
2018-02-21 RPUlux: ^1
2018-02-22 RPUlux: ^1 schmatic update
2018-03-11 K3 latching solenoid driver board
2018-03-28 RPUlux: ^2
    note ^1 also works, just need lbl's fixed, the SMPS overhaul was not
    needed.
2018-05-27 RPUno: ^9
2018-06-05 K3: ^1
    a previous version to look at.
2018-07-22 RPUadpt: ^6
    meme is "managed mulitdrop serial"
2018-09-09 USBuart: USB bridge
2018-09-09 485tx_en: multi-drop the easy way
2019-02-21 RPUpi and OneShot
2019-05-17 ICSP: in circuit programming of avr
2019-07-10 ICSP: ^3 !tested but low risk. ^2 is good /w jumper this adds
    nodes MISO & MIS0 are jumperd so only MISO are on ^3
2019-08-15 Gravimetric: ^0
    This is no Sitara but did that board ever get done?
2019-09-21 PiUpdi: ^0 reviewing
2019-09-21 PiUpdi: remove note
2020-07-16 prep to use as my regular repo
    I've been using some old hg repo's but I think Git and GitHub will work fine so it is time to move over
2020-07-16 ignore Eagle file locks and backup files
2020-07-17 Gravimetric: ^2 wip
2020-07-17 Gravimetric: ^2 oshpark accepted file, now reviewing
2020-07-19 PiUpdi: wip, swaping mcu to 128da (an xmega4 core)
2020-07-20 PiUpdi: ^1 layout wip
    serial crossover error fixed
2020-07-21 PiUpdi: review
2020-07-30 RPUftdi: remove
2020-07-31 RPUusb: got names mixed up on last checkin
2020-08-11 CCsm: small current source with thermal fold-back
2020-08-12 CCmid: schematic
2020-08-12 CCmid: referance values
2020-08-15 Buck: layout done
2020-08-16 PWM: ^0 boards on my assemby bench
2020-08-17 Lux: status
2020-08-17 Lux: markdown
2020-08-17 Lux: use vscode to see markdown
2020-08-21 RPUusb: readme
2020-08-21 RPUusb: status
2020-08-29 RPUusb: pin names on schematic match io_enum
2020-11-12 MacGyver: ^2 wip
2020-11-16 MacGyger: manager will be avr-db, remove spi
2020-11-17 MacGyver: remove rts/cts since no bootloader
2020-11-18 MacGyver: starting layout
2020-11-19 MacGyver: layout wip
2020-11-20 MacGyver: layout wip+
2020-11-22 MacGyver: layout wip++
2020-11-23 MacGyver: layout done, bom is next
2020-12-11 macgyver: layout done, needs reviewing
2021-01-22 reviewing elec mech stuff for fluid power
2021-11-15 PIC16 board for evaluating some parts
2021-11-16 PIC16
    8pin, 14pin, and 20pin will work, just keep pin 1 fixed.
2021-11-17 PIC16: add three switches
2021-11-21 Buck: looking at the inductor
2021-11-25 CCmid: ic is obsolete
2021-12-08 CCmid: fix obsolete part, set up for bat chrg
2021-12-11 CCmid: rm facing 10uF, add tvs, check inrush
    that bulk voltage peak is a problem when I use the inductor to limit inrush
2021-12-19 CCmid: fix inrush on schm
    inrush 3A6 with 36V step
2022-01-09 CCmid: bom, surge sim
2022-02-10 PIC16: schematic
